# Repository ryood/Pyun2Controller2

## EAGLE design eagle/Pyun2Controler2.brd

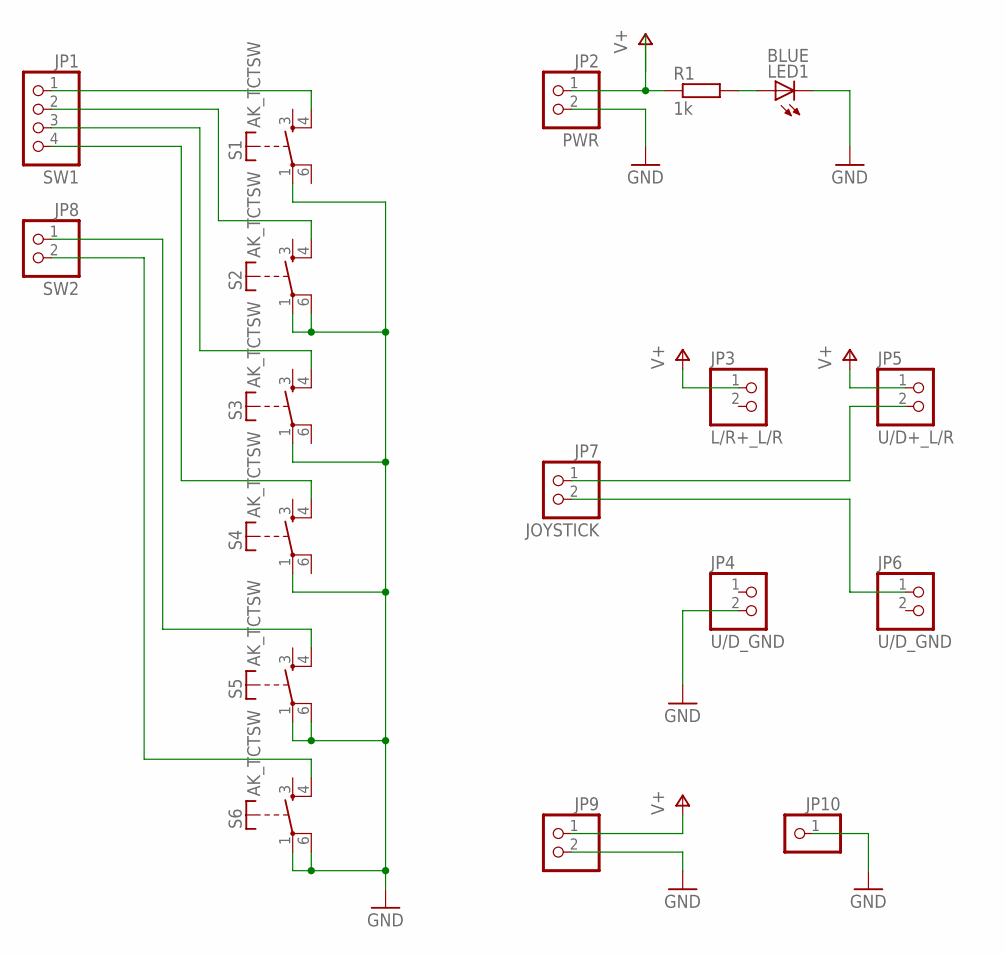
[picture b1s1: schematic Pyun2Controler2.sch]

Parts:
JP1: SW1; 1X04/90
JP2: PWR; 1X02/90
JP3: L/R+_L/R; 1X02
JP4, JP6: U/D_GND; 1X02
JP5: U/D+_L/R; 1X02
JP7: JOYSTICK; 1X02/90
JP8: SW2; 1X02/90
JP9: PINHD-1X2/90; 1X02/90
JP10: PINHD-1X1; 1X01
LED1: BLUE; LED3MM
R1: 1k; 0207/7
S1, S2, S3, S4, S5, S6: AK_TCTSW; TME1

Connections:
GND: JP2.2, JP4.2, JP9.2, JP10.1, LED1.K (C), S1.1, S2.1, S2.6, S3.1, S4.1, S5.1, S5.6, S6.1, S6.6
unnamed: JP1.1, S1.4 (S)
unnamed: JP1.2, S2.4 (S)
unnamed: JP1.3, S3.4 (S)
unnamed: JP1.4, S4.4 (S)
unnamed: LED1.A, R1.2
unnamed: JP5.2, JP7.1
unnamed: JP6.1, JP7.2
unnamed: JP8.1, S5.4 (S)
unnamed: JP8.2, S6.4 (S)
V+: JP2.1, JP3.1, JP5.1, JP9.1, R1.1

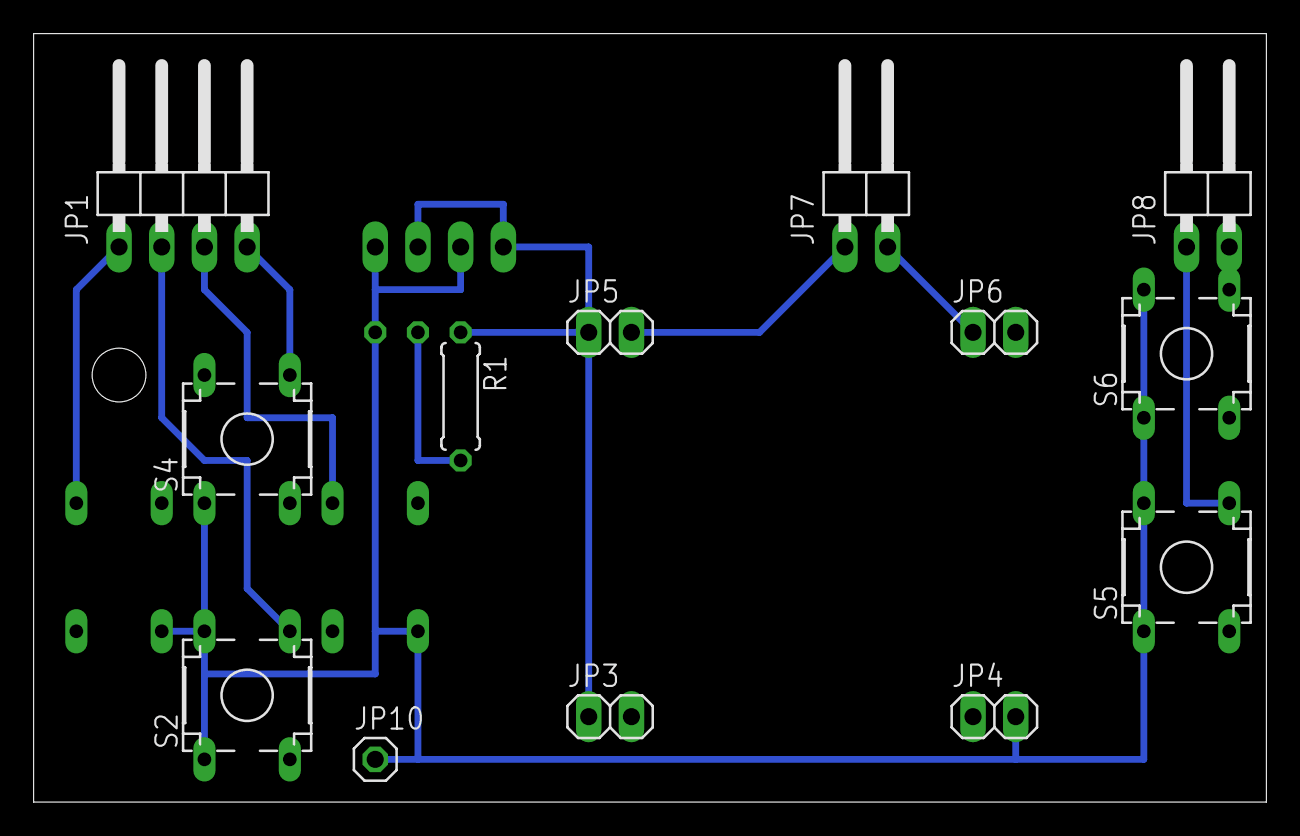
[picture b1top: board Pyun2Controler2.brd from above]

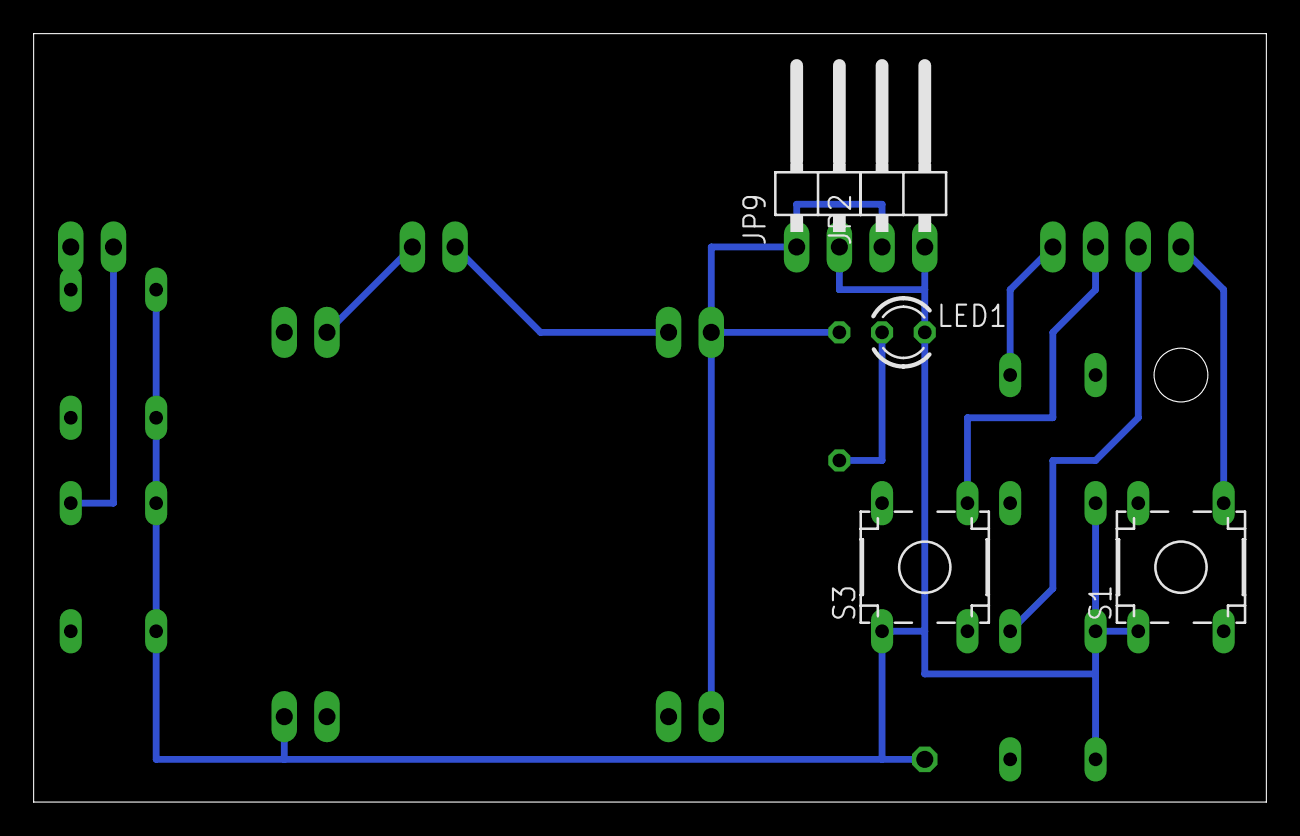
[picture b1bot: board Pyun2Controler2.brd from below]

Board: 2 copper layers, 73.3 x 45.7 mm, 18 parts (5 on the bottom side), 11 nets.

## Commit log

2015-07-25 Updated: PyunPyun controller 2 Case.dwg
2015-07-25 ケース加工図： Holeサイズ拡大
2015-07-28 ケース内配線図追加
2015-07-28 ケース加工図、横穴を追加
2015-07-28 Arduinoのテストプログラムを追加
